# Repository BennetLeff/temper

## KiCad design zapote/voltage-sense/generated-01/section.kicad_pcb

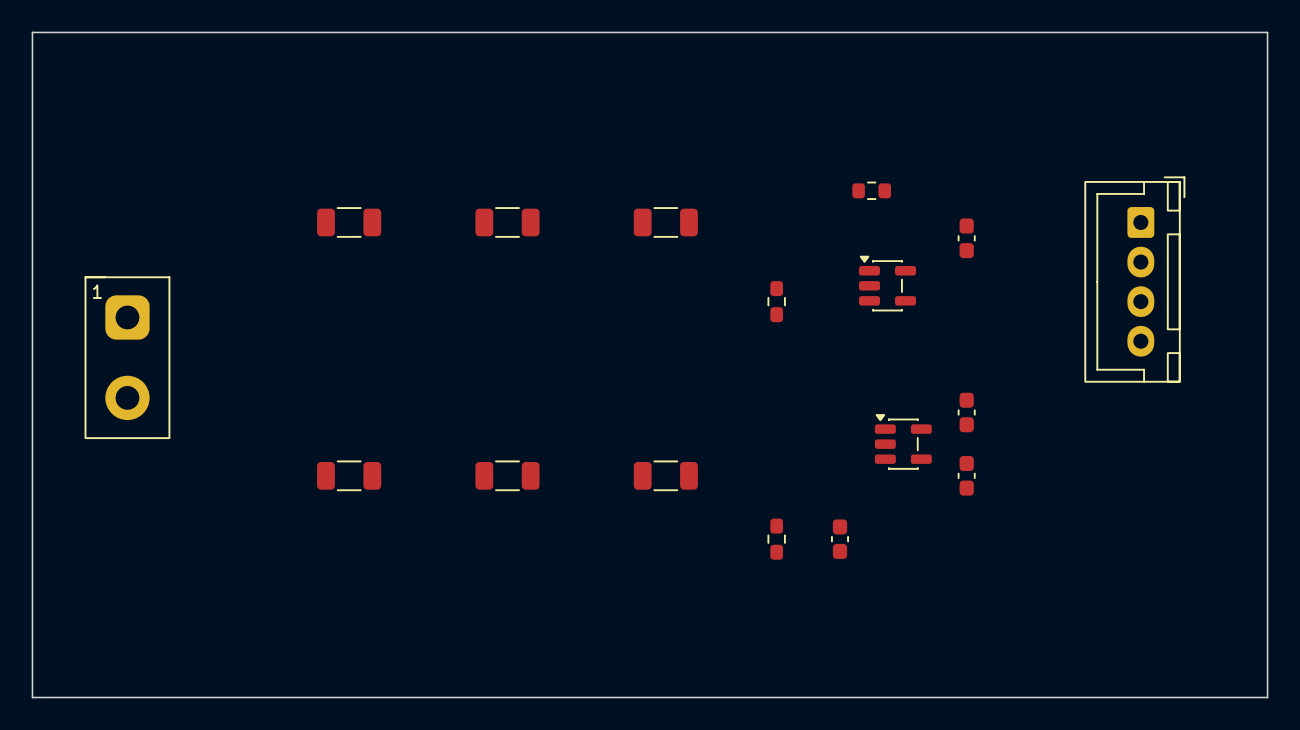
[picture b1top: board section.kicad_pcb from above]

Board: 6 copper layers, 78.0 x 42.0 mm, 17 parts (0 on the bottom side), 11 nets, no tracks yet.

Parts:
C1, C2, C3, C4: 100nF +/- 10%; C_0603_1608Metric
J1: 691253500002; VoltageInput_691253500002
J2: B4B-XH-A(LF)(SN); JST_XH_B4B-XH-A_1x04_P2.50mm_Vertical
R1, R2, R3: 430kohm +/- 1%; R_1206_3216Metric
R4: 16.9kohm +/- 0.1%; R_0603_1608Metric
R5: 487kohm +/- 0.1%; R_0603_1608Metric
R6, R7, R8: 300kohm +/- 1%; R_1206_3216Metric
R9: 10kohm +/- 1%; R_0603_1608Metric
U1: TLV3201AIDBVR; SOT-23-5
U2: REF2025AIDDCR; SOT-23-5

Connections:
+3V3: C2.1, C3.1, J2.1, U1.5, U2.3, U2.4
ADC_MID1: R6.2, R7.1
ADC_MID2: R7.2, R8.1
BUS_MON: C1.1, J2.4, R8.2, R9.1
BUS_PLUS: J1.1, R1.1, R6.1
BUS_RETURN: C1.2, C2.2, C3.2, C4.2, J1.2, J2.2, R4.2, R9.2, U1.2, U2.2
OVP_FAULT: J2.3, R5.2, U1.1
OVP_MID1: R1.2, R2.1
OVP_MID2: R2.2, R3.1
OVP_SENSE: R3.2, R4.1, R5.1, U1.3
VREF_2V5: C4.1, U1.4, U2.5
